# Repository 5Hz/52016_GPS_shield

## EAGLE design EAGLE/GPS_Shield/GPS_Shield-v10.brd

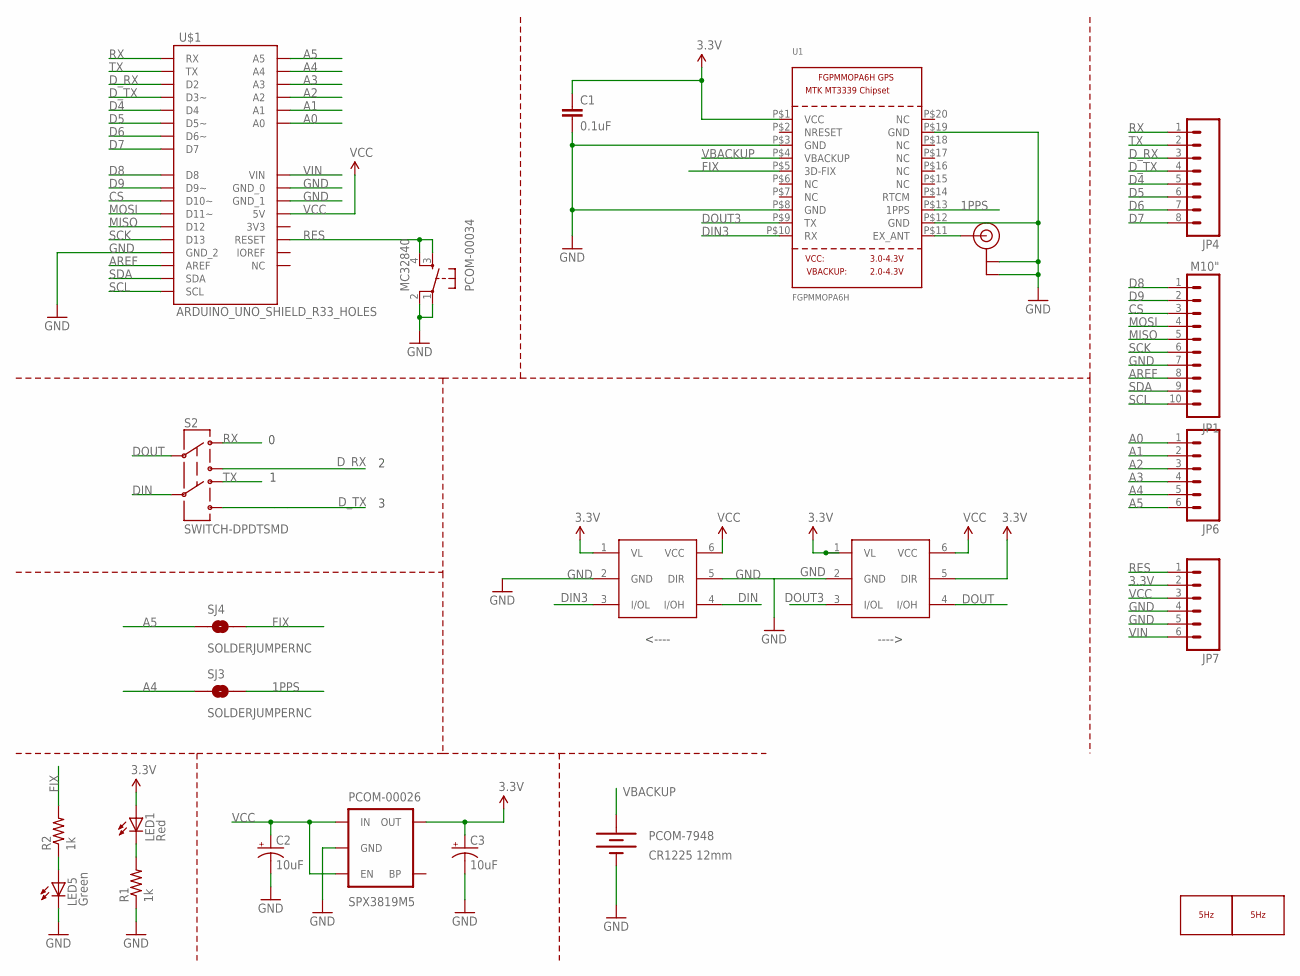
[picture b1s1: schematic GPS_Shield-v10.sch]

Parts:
C1: 0.1uF; 0603-CAP
C2, C3: 10uF; EIA3216
JP1: M10"; 1X10
JP4: M08; 1X08
JP6, JP7: M06SIP; 1X06
LED1: Red; LED-0603
LED5: Green; LED-0603
LOGO1: LOGO_5HZ_H_COOPER_15MM; 5HZ_LOGO_H_COOPER_15MM
LOGO2: LOGO_5HZ_H_20MM; 5HZ_LOGO_H_20MM
PCOM-00026: SPX3819M5; SOT23-5
PCOM-00034: MC32840; TACTILE_SWITCH_SMD
PCOM-7948: CR1225 12mm; BATTCON_12MM_PTH
R1, R2: 1k; 0603-RES
S2: SWITCH-DPDTSMD; AYZ0202
SJ3, SJ4: SOLDERJUMPERNC; SJ_2S
U1: FGPMMOPA6H
U$1: ARDUINO_UNO_SHIELD_R33_HOLES; UNO_R3_SHIELD_3_HOLES_NO_SILK
U$7, U$8: MAX337; SOT-363
U$20: U.FL

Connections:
1PPS: SJ3.2, U1.P$13 (1PPS)
3.3V: C1.1, C3.A (+), JP7.2, LED1.A, PCOM-00026.5 (OUT), U1.P$1 (VCC), U$7.1 (VL), U$8.1 (VL), U$8.5 (DIR)
A0: JP6.1, U$1.A0
A1: JP6.2, U$1.A1
A2: JP6.3, U$1.A2
A3: JP6.4, U$1.A3
A4: JP6.5, SJ3.1, U$1.A4
A5: JP6.6, SJ4.1, U$1.A5
AREF: JP1.8, U$1.AREF
CS: JP1.3, U$1.D10 (D10~)
D4: JP4.5, U$1.D4
D5: JP4.6, U$1.D5 (D5~)
D6: JP4.7, U$1.D6 (D6~)
D7: JP4.8, U$1.D7
D8: JP1.1, U$1.D8
D9: JP1.2, U$1.D9 (D9~)
DIN: S2.5, U$7.4 (I/OH)
DIN3: U1.P$10 (RX), U$7.3 (I/OL)
DOUT: S2.2, U$8.4 (I/OH)
DOUT3: U1.P$9 (TX), U$8.3 (I/OL)
D_RX: JP4.3, S2.3, U$1.D2
D_TX: JP4.4, S2.6, U$1.D3 (D3~)
FIX: R2.2, SJ4.2, U1.P$5 (3D-FIX)
GND: C1.2, C2.C (-), C3.C (-), JP1.7, JP7.4, JP7.5, LED5.C, PCOM-00026.2 (GND), PCOM-00034.1, PCOM-00034.2, PCOM-7948.GND (-), R1.1, U1.P$3 (GND), U1.P$8 (GND), U1.P$12 (GND), U1.P$19 (GND), U$1.GND_0, U$1.GND_1, U$1.GND_2, U$7.2 (GND), U$7.5 (DIR), U$8.2 (GND), U$20.P$1 (GND), U$20.P$2 (GND)
MISO: JP1.5, U$1.D12
MOSI: JP1.4, U$1.D11 (D11~)
unnamed: LED1.C, R1.2
unnamed: U1.P$11 (EX_ANT), U$20.P$3 (SIGNAL)
unnamed: LED5.A, R2.1
RES: JP7.1, PCOM-00034.3, PCOM-00034.4, U$1.RES (RESET)
RX: JP4.1, S2.1, U$1.RX
SCK: JP1.6, U$1.D13
SCL: JP1.10, U$1.SCL
SDA: JP1.9, U$1.SDA
TX: JP4.2, S2.4, U$1.TX
VBACKUP: PCOM-7948.VCC@1 (+), U1.P$4 (VBACKUP)
VCC: C2.A (+), JP7.3, PCOM-00026.1 (IN), PCOM-00026.3 (EN), U$1.5V, U$7.6 (VCC), U$8.6 (VCC)
VIN: JP7.6, U$1.VIN

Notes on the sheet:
<----
---->

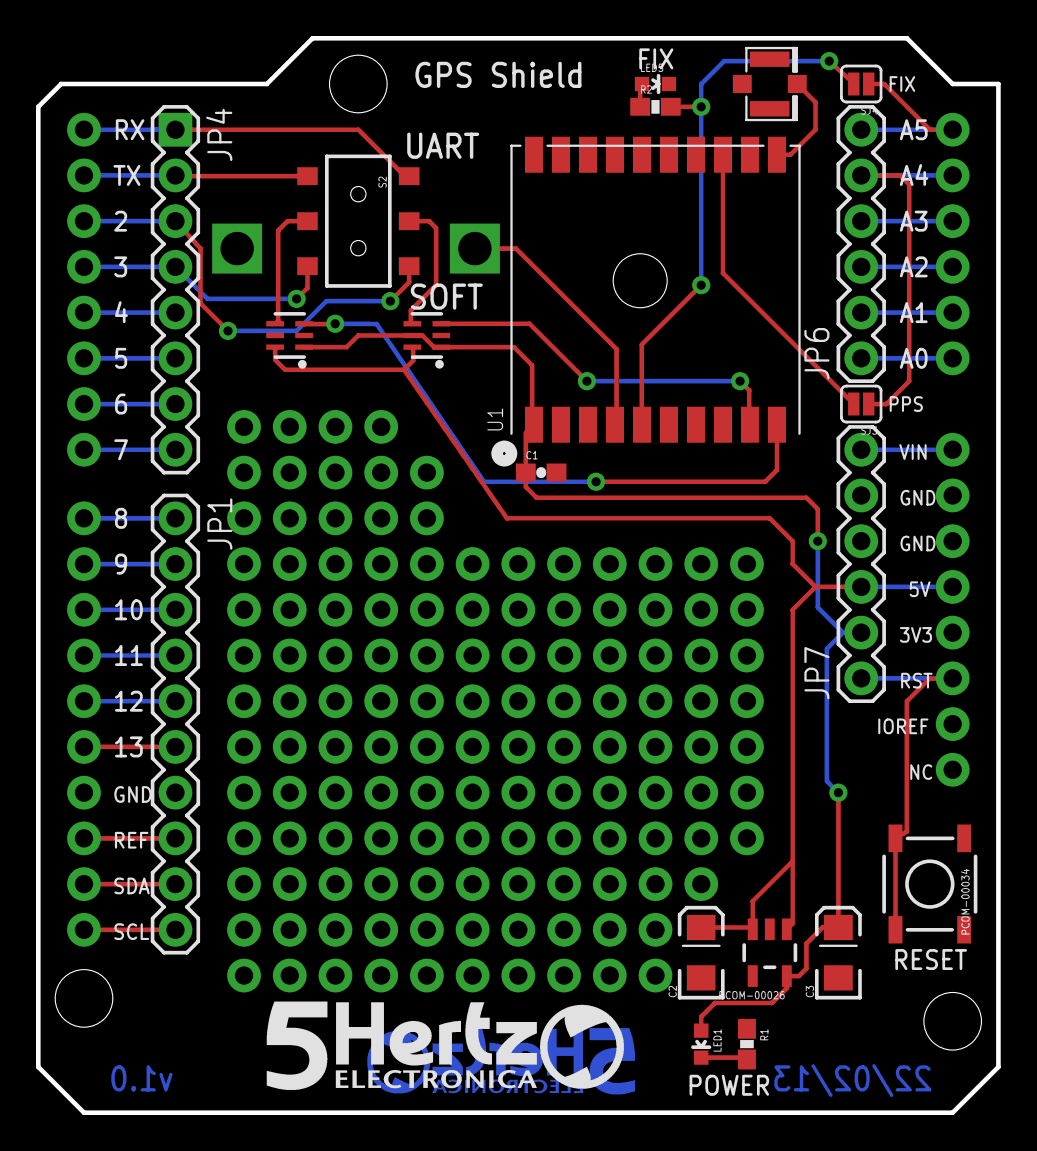
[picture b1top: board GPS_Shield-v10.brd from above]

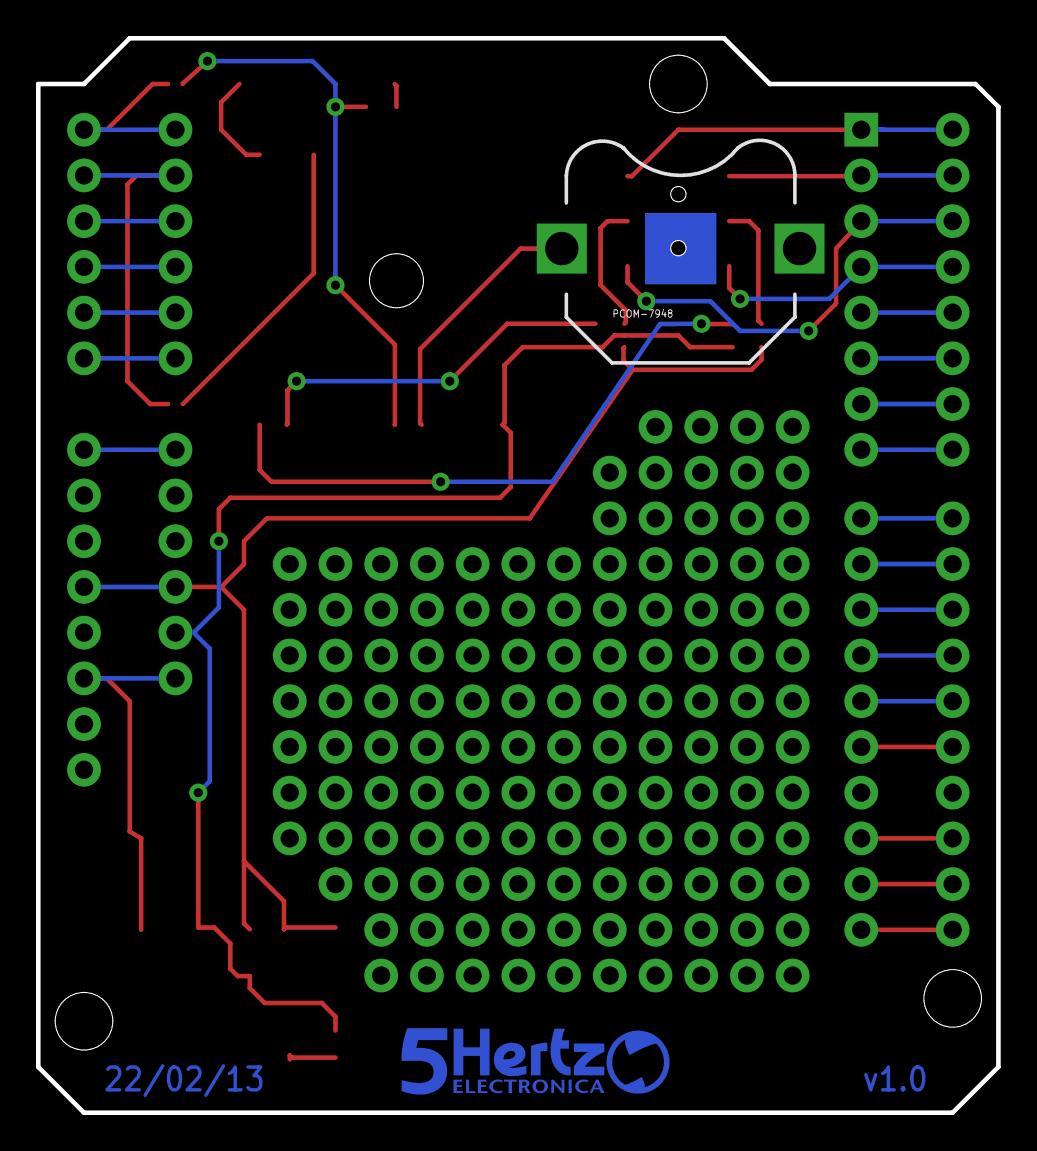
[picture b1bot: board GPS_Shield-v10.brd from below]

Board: 2 copper layers, 53.3 x 59.7 mm, 24 parts (2 on the bottom side), 38 nets.

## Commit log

2014-01-14 creación
